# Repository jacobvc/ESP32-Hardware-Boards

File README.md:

# Esp32 Dev Module Hardware Boards
This repository contains hardware and circuit board designs to simplify ESP32 Dev Module peripheral device connectivity

I think that I have about average circuit board design and soldering skills for an (older) mechanical engineer. As currently, mostly a hobbiest developer, I tend to develop reusable functionality focused circuit boards as opposed to project specific circuit boards. My soldering skills are OK for 0.1 inch center parts. 0805 surface mount parts are at or beyond my limit.

I am sharing these eagle board designs that I have found to be useful; mostly as a sort of tidy bridge between a breadboard and a project specific design. Unless otherwise specified, they are for (30 pin) ESP32 Dev Module boards.

All of the boards are designed using eagle, and any of them can be ordered in many ways, including by going to the [OSH park web site](https://oshpark.com/) and uploading the appropriate .brd file

## Esp32 Dev Module Pins
This design consists of two 15 pin pin headers; ESP32-LEFT and ESP32-RIGHT, with wires and labels corresponding to pin functionality. They are not 'connected' to one-another and are generally intended to be used as a quick start in laying out a board for one or the other side of an ESP32 Dev Module. 

## [ESP32 Lcd 3.5 Connectors](Lcd3.5Connectors)
This design connects the right side of an ESP32 Dev Module (ESP32-RIGHT) to a LCD touch screen display. The display uses all of the GPIOs on that side except two. A four pin connector supports connecting the display mounted SD socket using a shared SPI. The two unused ports are routed to a four pin I2C connector. 

[Used with this display](http://www.lcdwiki.com/3.5inch_SPI_Module_ILI9488_SKU:MSP3520)

## [ESP32 I/O Adapter](Esp32IoAdapt)
This design connects the left side of an ESP32 Dev Module to JST ZH 1.5mm keyed connectors. 

The connectors include
0.1 inch connectors
* 1 each 2 pin GS connector  (switch)
* 1 each 3 pin GVS connector (servo motor, etc). 

JST ZH 1.5mm keyed connectors. 
* 2 each 3 pin GVI connectors (potentiometer, etc). 
* 1 each 4 pin GVSS connector (serial port, I2C, etc)
* 1 each 5 pin GVIIS connectors (joystick, misc)
* 1 each 5 pin GVSSS connectors (joystick, misc)

Note:
*  GVS.. == Ground / 3v3 / Sense GPIO
*  GVI.. == Ground / 3v3 / Input only GPIO
## [ESP32 Audio / Relay Adapter](Esp32Relays)
This design connects left side of an esp32 Dev Module to:
* A three channel relay board
* A CD4066 based analog switch. Two channels of the CD4066 are connected to 3.5mm TRS (input / output) audio connectors, and the other two are available on a pair of 0.1 in center 3 pin headers.
* A 3 pin G5VS connector intended to be used for Neopixel Matrix Display
* Two 3 pin GVS connectors available for general use

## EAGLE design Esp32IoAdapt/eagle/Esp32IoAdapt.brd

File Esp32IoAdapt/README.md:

# ESP32 I/O Adapter

A relatively small footprint approach to make the I/O pins on the "LEFT_SIDE" of a ESP32 Dev Module available.

Consists of circuit board designs, a (src) header file, and examples.

## Boards
An Esp32IoAdapt board, supported by two other trivial boards to ease connectivity with thumb joysticks and slider potentiometers.

**Esp32IoAdapt** contains a ESP-32 "LEFT_SIDE" board that present the I/O pins on the left side of 
a ESP32 Dev Module as (mostly) JST ZH 1.5mm connectors.

**Joystick** contains a joystick adapter a joystick to the other end of a 5 pin connector.

**Slider** contains an adapter to mount and connect a 35mm slider potentiometer to the other end of a 3 pin connector.

### Esp32IoAdapt
0.1 inch connectors
* 1 each 2 pin GS connector  (switch)
* 1 each 3 pin GVS connector (servo motor, etc). 

JST ZH 1.5mm keyed connectors. The connectors include
* 2 each 3 pin GVI connectors (potentiometer, etc). 
* 1 each 4 pin GVSS connector (serial port, I2C, etc)
* 1 each 5 pin GVSSS connectors (joystick, misc)
* 1 each 5 pin GVIIS connectors (joystick, misc)

Note:
*  GVS.. == Ground / 3v3 / Sense GPIO
*  GVI.. == Ground / 3v3 / Input only GPIO
*  The "V" pins are all 3.3v, so they may not be suited for 5V devices such as 5V servo motors

Intended to be used with pre-built JST-ZH cables. 

### Joystick Adapter
A simple adapter board adapting straight through from 1.5 mm to 0.1 inch. Intended to connect thumb joystick via JST ZH connector 
or soldered wires from JST ZH cable.

### Slider Adapter
A simple adapter / mounting board for mounting a 35 mm slider potentiometer and connecting via JST ZH connector 
or soldered wires from JST ZH cable.

## src
src contains the Esp32IoAdapt.h header file, presented as a component

# Examples
[Esp32IoAdapt is used for the examples](https://github.com/jacobvc/ESP-Object-Messaging/tree/main/examples) in ESP-Object-Messaging.

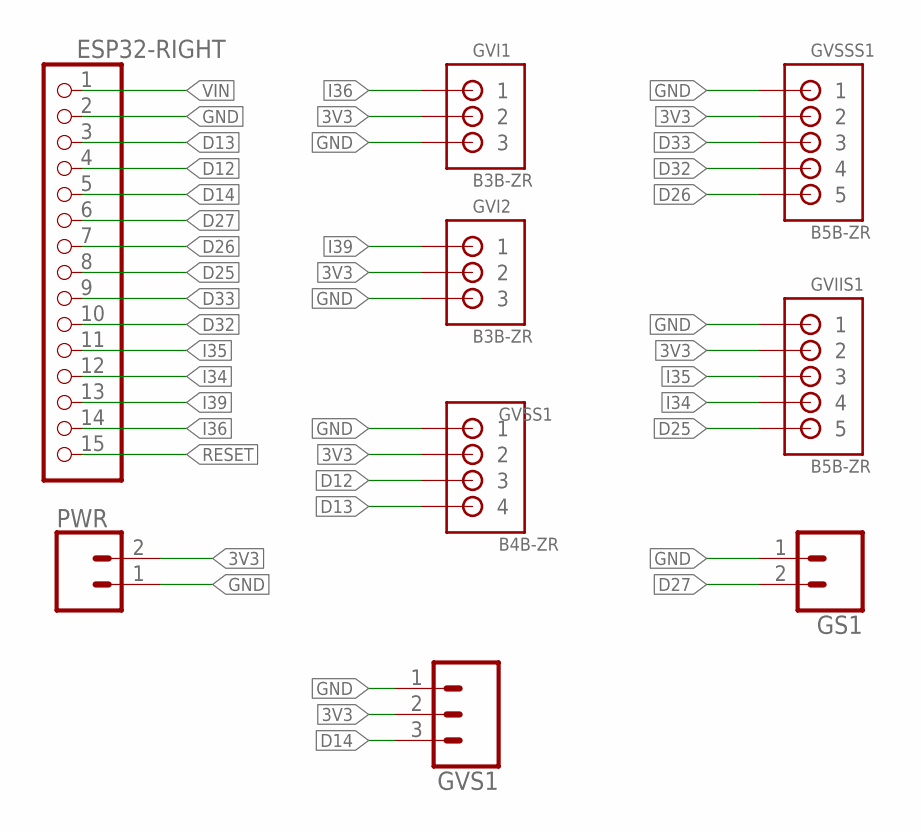
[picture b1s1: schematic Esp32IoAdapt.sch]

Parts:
ESP32-RIGHT: 0; 1X15
GS1: CONN_02; 1X02
GVI1, GVI2: B3B-ZR
GVIIS1: B5B-ZR
GVS1: CONN_03; 1X03
GVSS1: B4B-ZR
GVSSS1: B5B-ZR
PWR: CONN_02; 1X02

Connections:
3V3: GVI1.2, GVI2.2, GVIIS1.2, GVS1.2, GVSS1.2, GVSSS1.2, PWR.2
D12: ESP32-RIGHT.4, GVSS1.3
D13: ESP32-RIGHT.3, GVSS1.4
D14: ESP32-RIGHT.5, GVS1.3
D25: ESP32-RIGHT.8, GVIIS1.5
D26: ESP32-RIGHT.7, GVSSS1.5
D27: ESP32-RIGHT.6, GS1.2
D32: ESP32-RIGHT.10, GVSSS1.4
D33: ESP32-RIGHT.9, GVSSS1.3
GND: ESP32-RIGHT.2, GS1.1, GVI1.3, GVI2.3, GVIIS1.1, GVS1.1, GVSS1.1, GVSSS1.1, PWR.1
I34: ESP32-RIGHT.12, GVIIS1.4
I35: ESP32-RIGHT.11, GVIIS1.3
I36: ESP32-RIGHT.14, GVI1.1
I39: ESP32-RIGHT.13, GVI2.1
RESET: ESP32-RIGHT.15
VIN: ESP32-RIGHT.1

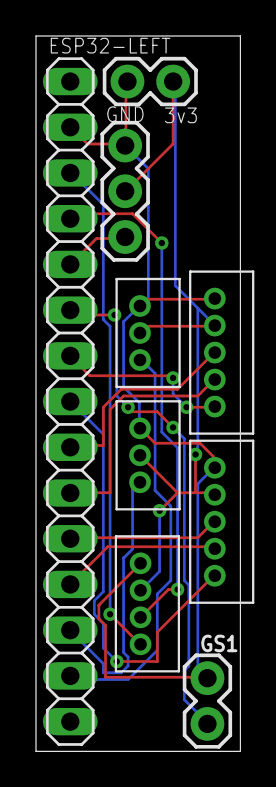
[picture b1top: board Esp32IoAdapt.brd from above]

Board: 2 copper layers, 11.4 x 39.7 mm, 9 parts (0 on the bottom side), 14 nets.

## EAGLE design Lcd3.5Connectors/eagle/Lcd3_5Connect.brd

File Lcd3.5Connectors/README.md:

# Lcd 3.5 Connectors (v4)
This design connects the right side of an ESP32 Dev Module to a LCD touch screen display. The display uses all of the GPIOs on that side except two. A four pin connector supports connecting the display mounted SD socket using a shared SPI. The two unused ports are routed to a four pin I2C connector. 

[Used with this display](http://www.lcdwiki.com/3.5inch_SPI_Module_ILI9488_SKU:MSP3520); Controller ili9488, Touch controller XPT2046

The hardware connections (for [LVGL V7 driver](https://github.com/lvgl/lv_port_esp32) is supported by these definitions in 'sdconfig'

    CONFIG_LV_TFT_DISPLAY_SPI_VSPI=y
    CONFIG_LV_DISP_SPI_MOSI=4
    # CONFIG_LV_DISPLAY_USE_SPI_MISO is not set
    CONFIG_LV_DISP_SPI_CLK=17
    CONFIG_LV_DISP_SPI_CS=19
    CONFIG_LV_DISP_PIN_DC=5
    CONFIG_LV_DISP_PIN_RST=18
    CONFIG_LV_TOUCH_DRIVER_PROTOCOL_SPI=y
    # CONFIG_LV_TOUCH_CONTROLLER_SPI_HSPI is not set
    CONFIG_LV_TOUCH_CONTROLLER_SPI_VSPI=y

    #
    # Touchpanel (XPT2046) Pin Assignments
    #
    CONFIG_LV_TOUCH_SPI_MISO=2
    CONFIG_LV_TOUCH_SPI_MOSI=4
    CONFIG_LV_TOUCH_SPI_CLK=17
    CONFIG_LV_TOUCH_SPI_CS=16
    # CONFIG_LV_TOUCH_PIN_IRQ is not set
    # end of Touchpanel (XPT2046) Pin Assignments

And separately to use the on-display-board SD Card Socket:

    #define LCD_BACKLIGHT_PIN 15
    #define SHARED_SPI_SD_CS_PIN 22
    #define SHARED_SPI_SD_HOST VSPI_HOST // same as LCD

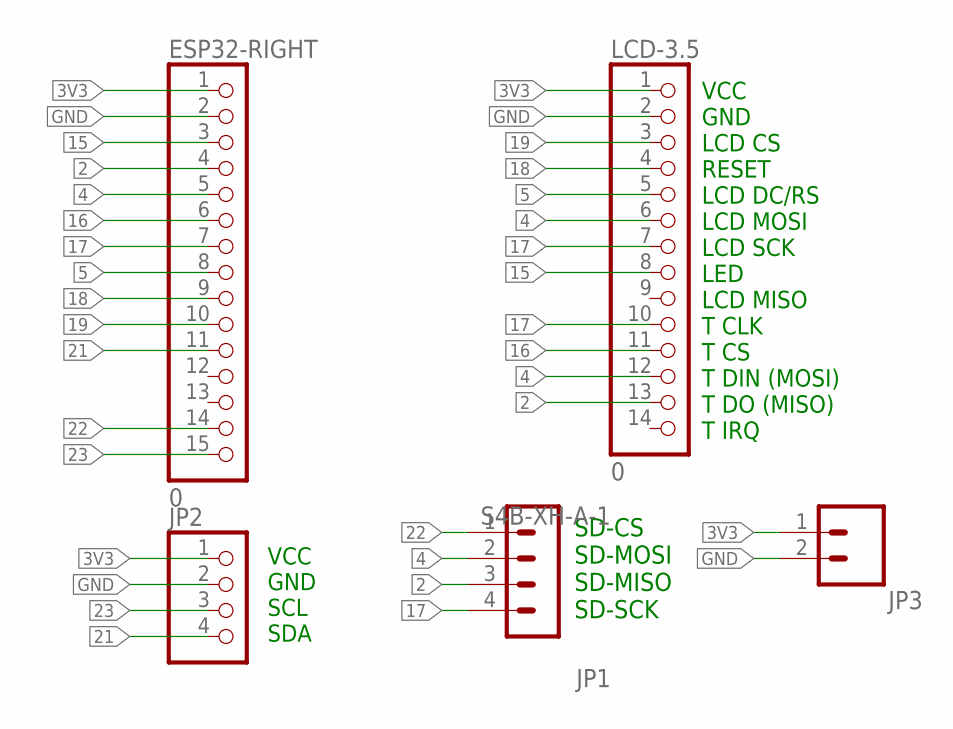
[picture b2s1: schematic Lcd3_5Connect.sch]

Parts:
ESP32-RIGHT: 0; 1X15
JP1: S4B-XH-A-1
JP2: PINHD-1X4; 1X04
JP3: CONN_02; 1X02
LCD-3.5: 0; 1X14

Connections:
2: ESP32-RIGHT.4, JP1.3, LCD-3.5.13
3V3: ESP32-RIGHT.1, JP2.1, JP3.1, LCD-3.5.1
4: ESP32-RIGHT.5, JP1.2, LCD-3.5.6, LCD-3.5.12
5: ESP32-RIGHT.8, LCD-3.5.5
15: ESP32-RIGHT.3, LCD-3.5.8
16: ESP32-RIGHT.6, LCD-3.5.11
17: ESP32-RIGHT.7, JP1.4, LCD-3.5.7, LCD-3.5.10
18: ESP32-RIGHT.9, LCD-3.5.4
19: ESP32-RIGHT.10, LCD-3.5.3
21: ESP32-RIGHT.11, JP2.4
22: ESP32-RIGHT.14, JP1.1
23: ESP32-RIGHT.15, JP2.3
GND: ESP32-RIGHT.2, JP2.2, JP3.2, LCD-3.5.2

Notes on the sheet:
VCC GND LCD CS RESET LCD DC/RS LCD MOSI LCD SCK LED LCD MISO T CLK T CS T DIN (MOSI) T DO (MISO) T IRQ
SD-CS SD-MOSI SD-MISO SD-SCK
VCC GND SCL SDA

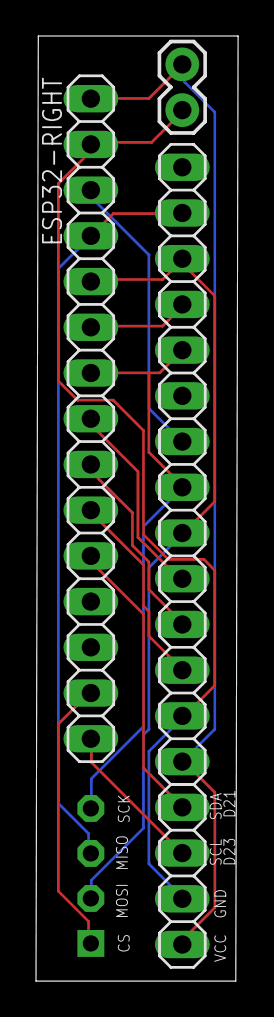
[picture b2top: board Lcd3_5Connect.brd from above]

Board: 2 copper layers, 11.2 x 52.5 mm, 5 parts (1 on the bottom side), 13 nets.

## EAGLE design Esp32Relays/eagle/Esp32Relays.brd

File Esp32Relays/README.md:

# Esp32 Relays Board
This design utilizes the left side of an ESP32 Dev Module for:

* A three channel relay board
* A CD4066 based analog switch. Two channels of the CD4066 are connected to 3.5mm TRS (input / output) audio connectors, and the other two are available on a pair of 0.1 in center 3 pin headers.
* A 3 pin (Ground, 5V, and Data on D32) connector intended to be used for Neopixel Matrix Display
* Two 3 pin (Ground, 3.3v, D25 or D26) connectors available for general use

A 3 pin Power connector is provided for **REQUIRED 3.3v input** (from the other side of the ESP32) and optional 5V power for when the system is not being powered by the ESP32 built in USB

Top View<br><br>
Bottom View<br>

## Components
The components required to assemble the board are:
* One each ESP32 WROOM Development Module
* One each 3 channel relay board
* One each 3 pin JSC SM Male connector with cable
* One each CD4066 ananlog switch
* Two each PJ-307 Audio jacks
* Two each (R1, R4) 4.7k 0805 resistors
* Four Each (R2, R3, R5, R6) 100k 0805 resistors
* Four Each (C1, C2, C3, C4) 1uf 0805 capacitors
* 0.1 center pin headers as desired

The board is designed to use this three channel relay, which requires a 5V supply but supports 3.3v logic.<br><br>

The assembly looks like this (with the larger components set in place but not soldered).<br>

The assembled components fit nicely into a 100 x 60 x 25 mm project box. The audio jacks are about 60.5 mm end to end, so you spread the case and they snap into place and help secure the assembly.<br>

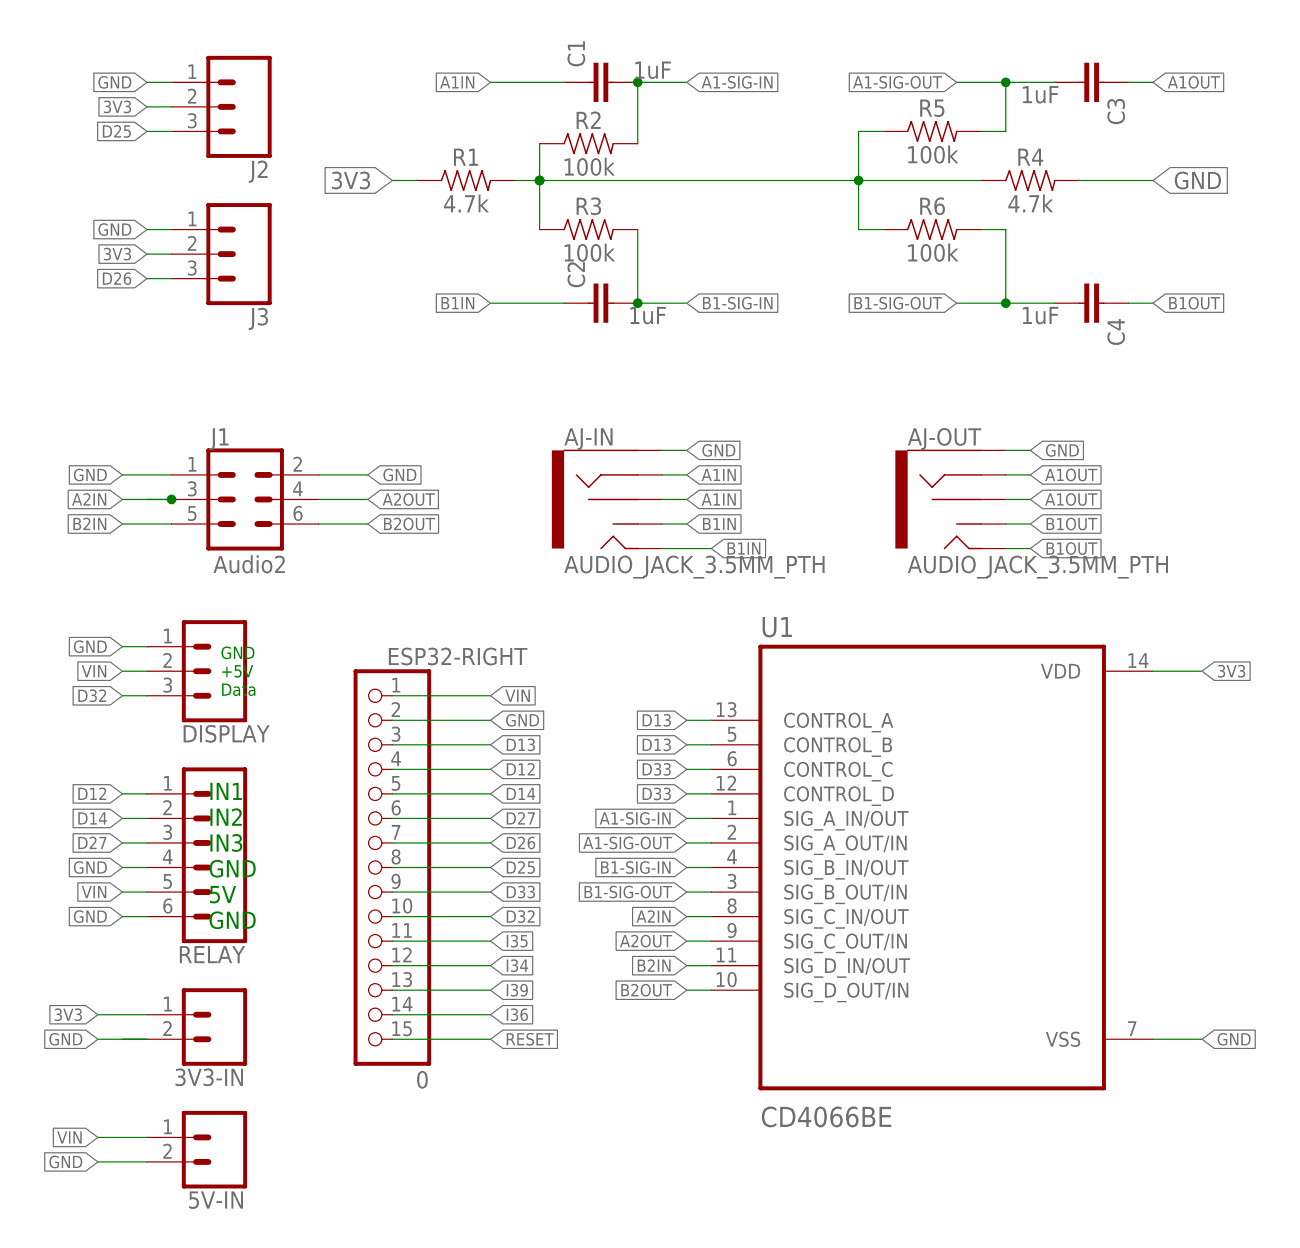
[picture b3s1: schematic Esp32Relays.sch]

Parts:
3V3-IN, 5V-IN: CONN_02; 1X02
AJ-IN: AUDIO_JACK_3.5MM_PTH; AUDIO-JACK
AJ-OUT: AUDIO_JACK_3.5MM_PTH; AUDIO-JACK
C1, C2, C3, C4: 1uF; 0805
DISPLAY: CONN_03; 1X03
ESP32-RIGHT: 0; 1X15
J1: Audio2; 2X3
J2, J3: CONN_03; 1X03
R1, R4: 4.7k; 0805
R2, R3, R5, R6: 100k; 0805
RELAY: CONN_06NO_SILK_FEMALE_PTH; 1X06_NO_SILK
U1: CD4066BE; DIP794W45P254L1969H508Q14

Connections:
3V3: 3V3-IN.1, J2.2, J3.2, R1.1, U1.14 (VDD)
A1-SIG-IN: C1.2, R2.2, U1.1 (SIG_A_IN/OUT)
A1-SIG-OUT: C3.2, R5.2, U1.2 (SIG_A_OUT/IN)
A1IN: AJ-IN.RING, AJ-IN.RSH, C1.1
A1OUT: AJ-OUT.RING, AJ-OUT.RSH, C3.1
A2IN: J1.3, U1.8 (SIG_C_IN/OUT)
A2OUT: J1.4, U1.9 (SIG_C_OUT/IN)
B1-SIG-IN: C2.2, R3.2, U1.4 (SIG_B_IN/OUT)
B1-SIG-OUT: C4.2, R6.2, U1.3 (SIG_B_OUT/IN)
B1IN: AJ-IN.TIP, AJ-IN.TSH, C2.1
B1OUT: AJ-OUT.TIP, AJ-OUT.TSH, C4.1
B2IN: J1.5, U1.11 (SIG_D_IN/OUT)
B2OUT: J1.6, U1.10 (SIG_D_OUT/IN)
D12: ESP32-RIGHT.4, RELAY.1
D13: ESP32-RIGHT.3, U1.5 (CONTROL_B), U1.13 (CONTROL_A)
D14: ESP32-RIGHT.5, RELAY.2
D25: ESP32-RIGHT.8, J2.3
D26: ESP32-RIGHT.7, J3.3
D27: ESP32-RIGHT.6, RELAY.3
D32: DISPLAY.3, ESP32-RIGHT.10
D33: ESP32-RIGHT.9, U1.6 (CONTROL_C), U1.12 (CONTROL_D)
GND: 3V3-IN.2, 5V-IN.2, AJ-IN.SLEEVE, AJ-OUT.SLEEVE, DISPLAY.1, ESP32-RIGHT.2, J1.1, J1.2, J2.1, J3.1, R4.2, RELAY.4, RELAY.6, U1.7 (VSS)
I34: ESP32-RIGHT.12
I35: ESP32-RIGHT.11
I36: ESP32-RIGHT.14
I39: ESP32-RIGHT.13
unnamed: R1.2, R2.1, R3.1, R4.1, R5.1, R6.1
RESET: ESP32-RIGHT.15
VIN: 5V-IN.1, DISPLAY.2, ESP32-RIGHT.1, RELAY.5

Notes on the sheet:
IN1 IN2 IN3 GND 5V GND
GND +5V Data

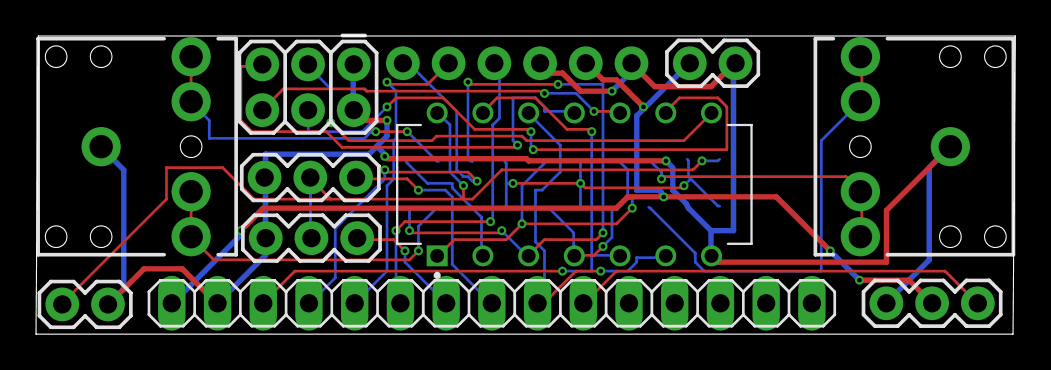
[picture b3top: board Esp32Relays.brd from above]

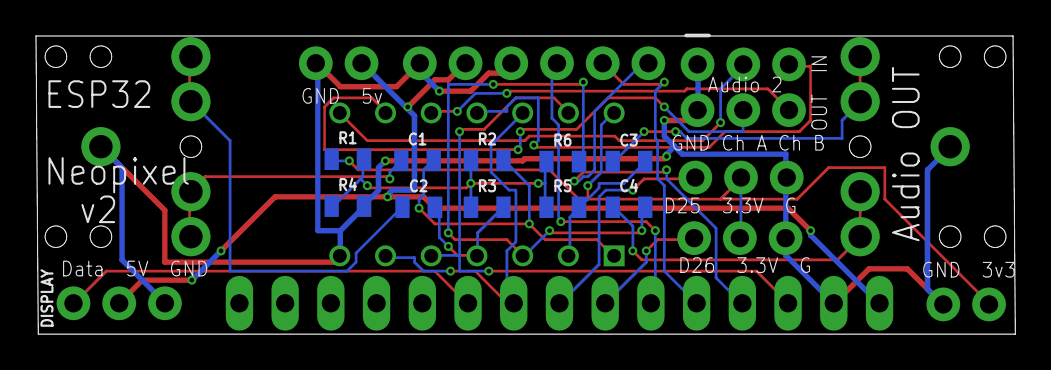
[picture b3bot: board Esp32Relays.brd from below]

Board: 2 copper layers, 54.4 x 16.6 mm, 21 parts (10 on the bottom side), 24 nets.

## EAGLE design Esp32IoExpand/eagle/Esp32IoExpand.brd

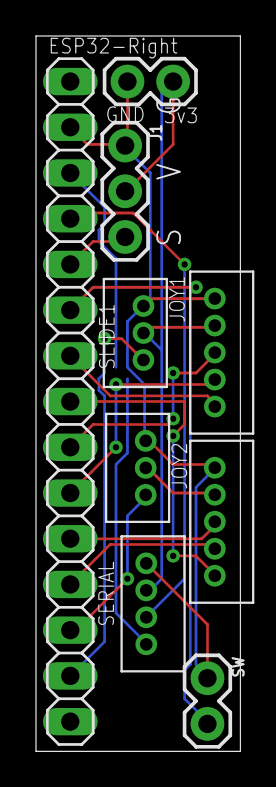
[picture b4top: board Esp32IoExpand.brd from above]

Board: 2 copper layers, 11.4 x 39.7 mm, 9 parts (0 on the bottom side), 14 nets.

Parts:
ESP32-RIGHT: 0; 1X15
J1: 1X03
JOY1, JOY2: B5B-ZR
PWR: 1X02
SERIAL: B4B-ZR
SLIDE1, SLIDE2: B3B-ZR
SW: 1X02

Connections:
3V3: J1.2, JOY1.2, JOY2.2, PWR.2, SERIAL.2, SLIDE1.2, SLIDE2.2
D12: ESP32-RIGHT.4, SERIAL.3
D13: ESP32-RIGHT.3, SERIAL.4
D14: ESP32-RIGHT.5, J1.3
D25: ESP32-RIGHT.8, JOY2.5
D26: ESP32-RIGHT.7, JOY1.5
D27: ESP32-RIGHT.6, SW.2
D32: ESP32-RIGHT.10, JOY1.4
D33: ESP32-RIGHT.9, JOY1.3
GND: ESP32-RIGHT.2, J1.1, JOY1.1, JOY2.1, PWR.1, SERIAL.1, SLIDE1.1, SLIDE2.1, SW.1
I34: ESP32-RIGHT.12, JOY2.4
I35: ESP32-RIGHT.11, JOY2.3
I36: ESP32-RIGHT.14, SLIDE1.3
I39: ESP32-RIGHT.13, SLIDE2.3

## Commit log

2022-06-15 Initial Checkin first 3 boards
2022-06-15 Rename visca_1.brd to RightSideIoConnectors.brd
2022-06-15 Rename visca_1.sch to RightSideIoConnectors.sch
2022-06-15 Added images
2022-06-15 Fixed directory typo
2022-06-15 Moved images to assets
2022-06-15 Resized board images
2022-07-04 Minor silkscreen tweak
2022-07-04 Renaming and silkscreen update
2022-07-04 Silkscreen tweak
2022-07-04 Silkscreen
2022-07-04 Added esp32 relays
2022-07-04 Removed unwanted files
2022-07-04 Neopixel board
2022-07-04 Schematic update
2022-07-10 Changed cap values and some labels
2022-07-13 Updated images
2023-03-11 Changed connector orientation
2023-03-21 Added 0.50 space
2023-03-21 Added 3v3 / GND connection
2023-03-22 Update Lcd3_5Connect.brd
    Rotated 3.3v connector
2023-03-22 Added 3v connector space
2023-03-24 Corrected left vs right nomenclature
2023-03-27 Added brightness GPIO
    and removed - unused - Touch IRQ pin
2023-03-27 Updated board image
2023-03-30 Minor dimension tweak
2023-03-30 Work on scad output
2023-04-01 Comments
2023-04-03 Renamed connectors
2023-04-03 Adjusted labels
2023-04-03 More connector labelling
2023-04-24 Added header and example
2023-04-26 Work on example
2023-04-28 Work on joy.js
2023-04-28 Debugging
    work on web page, changed main to C++
2023-04-28 Debugging
2023-04-28 Updating web page
2023-04-29 Adding LvglHost
2023-04-30 Work on lvgl and ui_bind.py
2023-04-30 Refactor ObjMsgData
2023-05-01 More on lvglHost
2023-05-01 Work on lvglHost
2023-05-01 Refining LvglHost
2023-05-02 More LvglHost work
2023-05-02 debugged and moved files
    Refactored some of the operations and locations.
    Moved LvglHost (and others) from development location to this repository.
2023-05-02 Reorganize layout
2023-05-02 Updated project name
2023-05-02 Update example
2023-05-03 Work on GpioHost
2023-05-04 Reorganize file layout
2023-05-04 Updated Squareline studio
2023-05-04 Progress on GpioHost
2023-05-08 Added lvgl virtual consumer
2023-05-08 Misc tweaking
2023-05-11 Code style naming cleanup
2023-05-11 Updated ui_bind.py output
2023-05-15 Refactoring
2023-05-16 Implemented forward
2023-05-18 Added joystick and slider boards
2023-05-19 Made Esp32IoAdapt into component
2023-05-19 resize images
2023-05-23 Added GPIO Output to example

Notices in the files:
parts and their libraries:
SparkFun-Connectors: Licensing: Creative Commons ShareAlike 4.0 International - https://creativecommons.org/licenses/by-sa/4.0
